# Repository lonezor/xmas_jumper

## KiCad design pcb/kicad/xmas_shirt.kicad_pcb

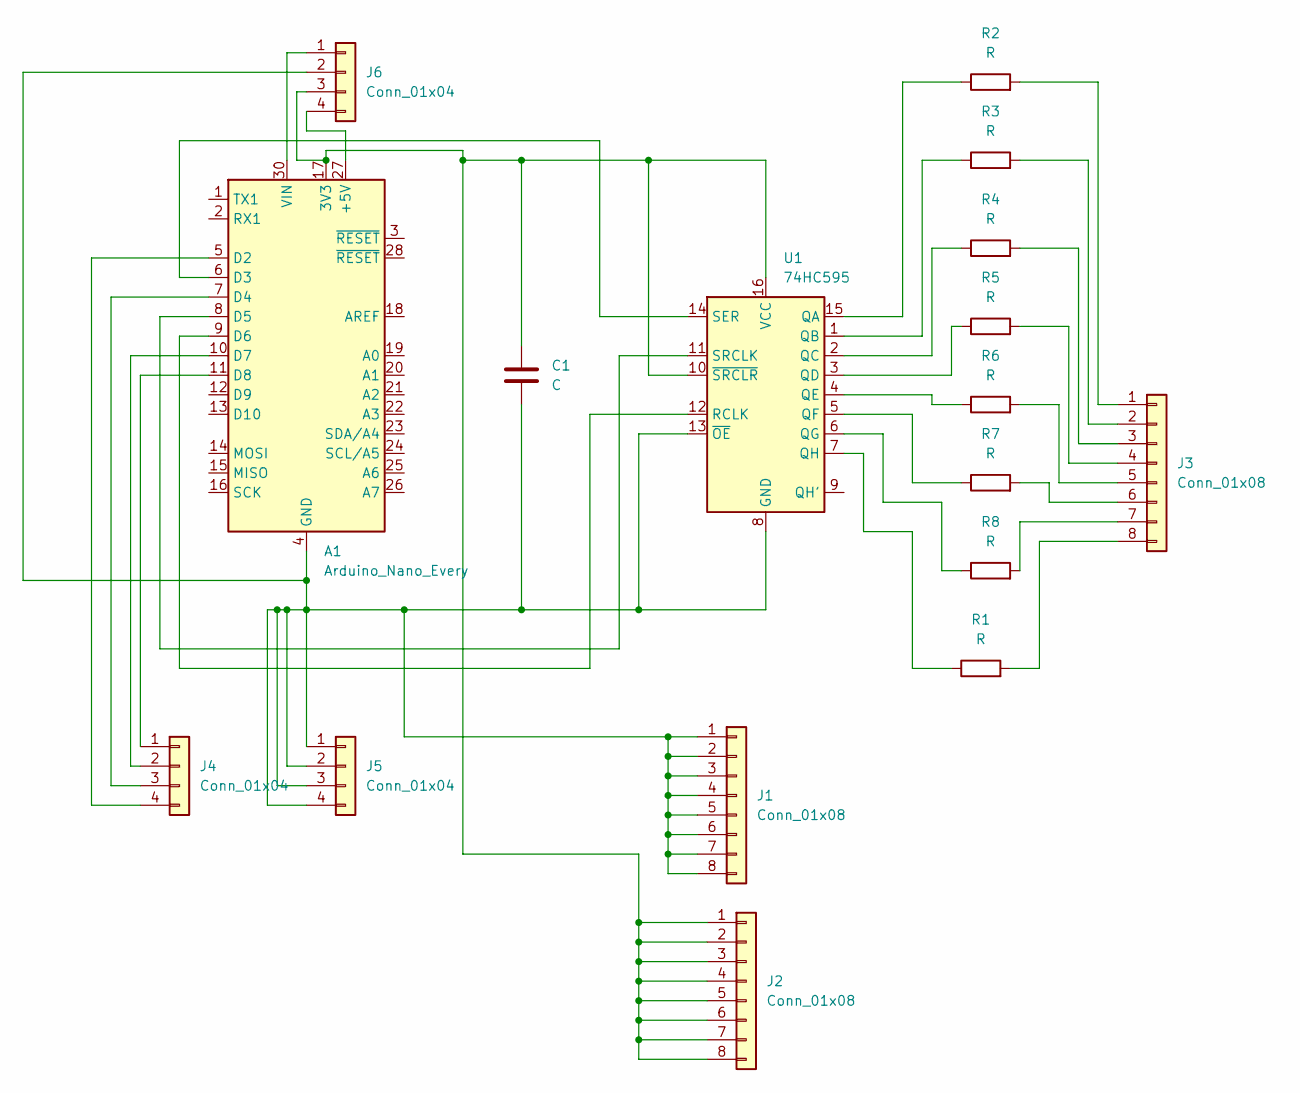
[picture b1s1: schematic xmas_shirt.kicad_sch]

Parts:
A1: Arduino_Nano_Every; Arduino_Nano
C1: C; CP_Radial_Tantal_D5.5mm_P2.50mm
J1, J2, J3: Conn_01x08; PinHeader_1x08_P2.54mm_Vertical
J4, J5, J6: Conn_01x04; PinHeader_1x04_P2.54mm_Vertical
R1, R2, R3, R4, R5, R6, R7, R8: R; R_Axial_DIN0207_L6.3mm_D2.5mm_P7.62mm_Horizontal
U1: 74HC595; DIP-16_W7.62mm_Socket

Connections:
unnamed: A1.17 (3V3), C1.1, J2.1, J2.2, J2.3, J2.4, J2.5, J2.6, J2.7, J2.8, J6.3, U1.10 (~SRCLR), U1.16 (VCC)
unnamed: A1.27 (+5V), J6.4
unnamed: A1.5 (D2), J4.4
unnamed: A1.6 (D3), U1.14 (SER)
unnamed: A1.7 (D4), J4.3
unnamed: A1.8 (D5), U1.11 (SRCLK)
unnamed: A1.9 (D6), U1.12 (RCLK)
unnamed: A1.10 (D7), J4.2
unnamed: A1.11 (D8), J4.1
unnamed: A1.30 (VIN), J6.1
unnamed: A1.4 (GND), A1.29 (GND), C1.2, J1.1, J1.2, J1.3, J1.4, J1.5, J1.6, J1.7, J1.8, J5.1, J5.2, J5.3, J5.4, J6.2, U1.8 (GND), U1.13 (~OE)
unnamed: J3.1, R2.2
unnamed: J3.2, R3.2
unnamed: J3.3, R4.2
unnamed: J3.4, R5.2
unnamed: J3.5, R6.2
unnamed: J3.6, R7.2
unnamed: J3.7, R8.2
unnamed: J3.8, R1.2
unnamed: R2.1, U1.15 (QA)
unnamed: R3.1, U1.1 (QB)
unnamed: R4.1, U1.2 (QC)
unnamed: R5.1, U1.3 (QD)
unnamed: R6.1, U1.4 (QE)
unnamed: R7.1, U1.5 (QF)
unnamed: R8.1, U1.6 (QG)
unnamed: R1.1, U1.7 (QH)

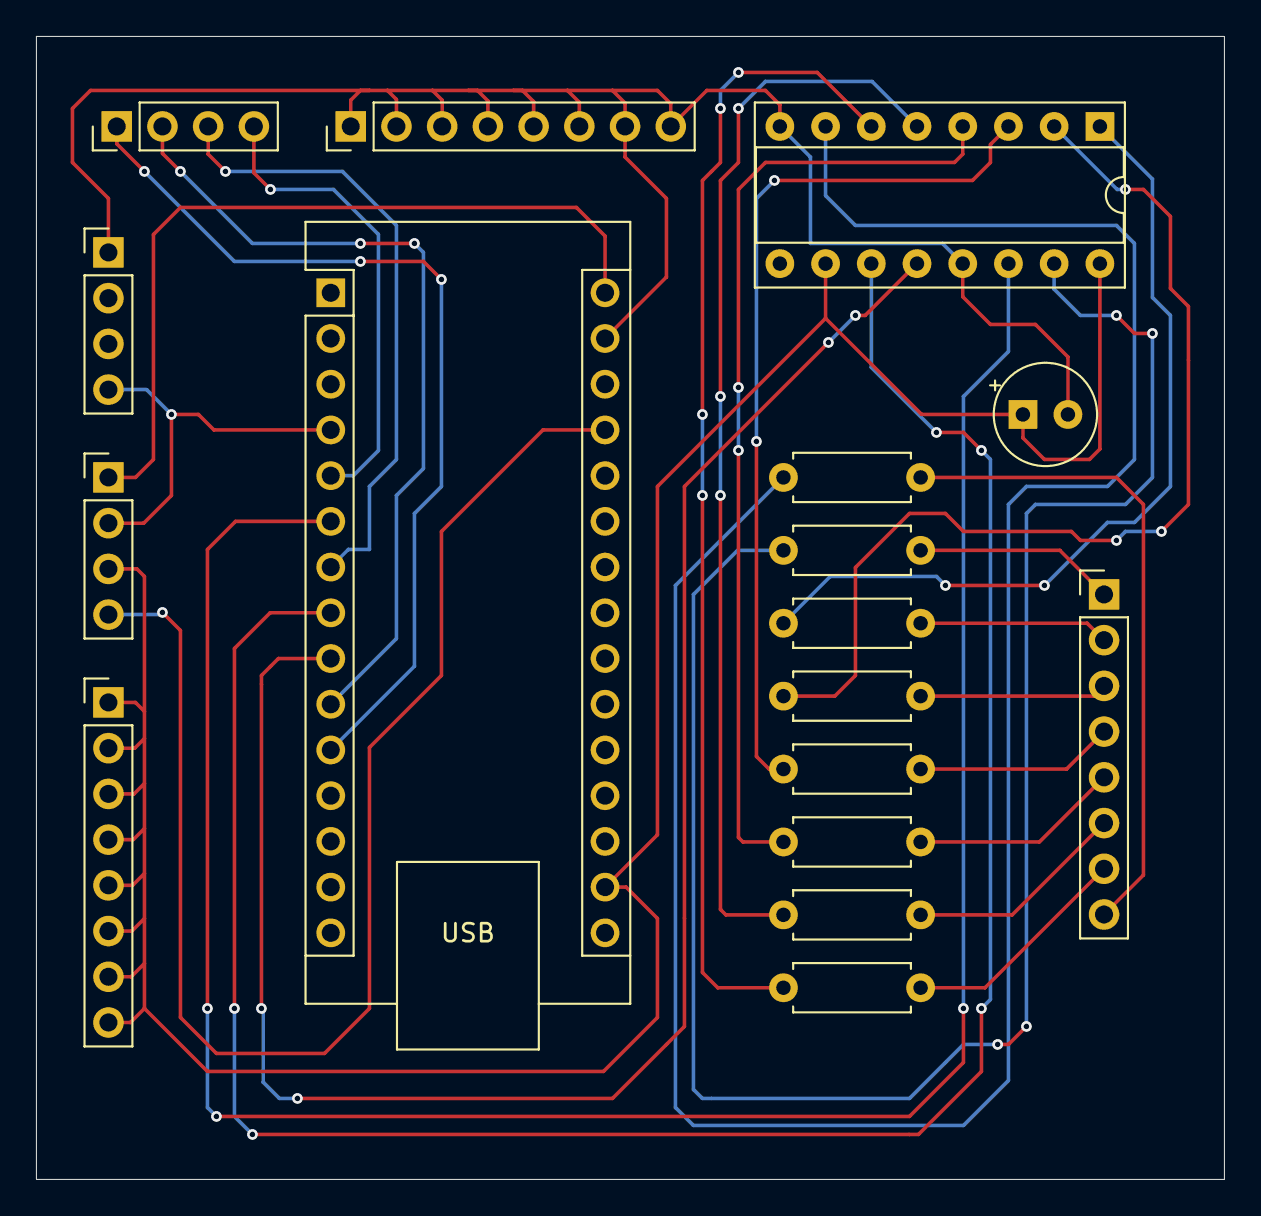
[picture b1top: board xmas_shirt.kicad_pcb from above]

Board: 2 copper layers, 66.0 x 63.5 mm, 17 parts (0 on the bottom side), 27 nets.

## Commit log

2024-12-03 Add README.md
2024-12-03 Add PCB files
2024-12-03 Add Arduino nano controller code
2024-12-03 Add battery unit blender file
